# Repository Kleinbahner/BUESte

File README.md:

# BUESte

## Getting parts:
Parts have been put into Reichelt.de parts baskets. Select a basket, specify the number of times you need the parts and put them in your shopping basket.
The following parts lists are available

- [bue: main pcb](https://www.reichelt.de/my/1827413)
- [bue: button boxes](https://www.reichelt.de/my/1832678)
- [bue: detectors](https://www.reichelt.de/my/1832677)
- [bue: cables](https://www.reichelt.de/my/1832680) select the cables suitable for your setup

Lists are also stored [here](https://github.com/Kleinbahner/BUESte/tree/main/doc/reichelt)

## Manuals:
Manual for main pcb assembly: [main pcb manual](https://github.com/Kleinbahner/BUESte/blob/main/doc/Manual%20(DE)%20Bahn%C3%BCbergang%20Platine%20v2.pdf)

Manual for boxes: [boxes manual](https://github.com/Kleinbahner/BUESte/blob/main/doc/Manual-DE-Box.pdf), [drilling template](https://github.com/Kleinbahner/BUESte/blob/main/doc/drill%20template%20bue.pdf)

Manual for detector: to follow

## Software

Manual for programming the Arduino: [Arduino programming](https://github.com/Kleinbahner/BUESte/blob/main/doc/Programmierung%20Arduino%20f%C3%BCr%20Bahn%C3%BCbergangssteuerung.pdf)

## Components
The railway crossing control unit consists of different components that can can be combined in various ways in order to suit the actual module layout requirements. The components will be described in more detail in the following sections.

### Mainboard

The main board is permanently installed near the railroad crossing. All other components are connected to the main board.

The flashing light signals for the railway crossing and the servos for the fences can be connected via terminal blocks. The control inputs are connected to further terminal blocks. There is also an amplifier for connecting a loudspeaker. The sounds can be stored on a microSD card. Power is supplied via an USB socket.

The two RJ45 sockets are used to connect the other components via a looped-through cable. All components can be connected to the same cable in any order. Star cabling is also possible. Alternatively, the inputs and outputs can also be connected directly to the terminal blocks if they are installed in the same module.

#### Pin assignement
All components must be connected to the main board. It has a number of screw and plug connections for this purpose. Ideally, the main board should be mounted near the railroad crossing itself so that many components such as the flashing signals, the light barrier for clear signaling and the loudspeaker can be connected directly. The following illustration provides an overview of the connection options.

The available signals and their meaning are listed here in detail. The output signals for the LED are driven with 5V. Corresponding series resistors must be added yourself!

| Signal | Direction | Activation | Purpose |
| ------ | --------- | ---------- | ------- |
| Loudspeaker | output | - | Connections for a small passive loudspeaker, maximum 1W |
| Servo_1 ... Servo_8 | output | Servo connections for the fences. Pin assignement (from boarder of PCB): - , +, pulse |
| UT-LED_1 | output | LED is on if the current sensor on the left track is disabled by the UT push button |
| UT-LED_2 | output | LED is on if the current sensor on the right track is disabled by the UT push button |
| Uebsig_1 | output | LED for the flashing signals of the left track |
| Uebsig_2 | output | LED for the flashing signals of the right track |
| Blink_1 ... Blink_4 | output | Flashing signals for the railroad crossing.  Blink_1 and 2 are phase shifted to Blink_3 and 4 |
| Bus_1 | output | Signals to attached remote components on the left track |
| Bus_2 | output | Signals to attached remote components on the right track |
| Strom_1 | input | LOW active | Input for the current sensor of the left track |
| Strom_2 | input | LOW active | Input for the current sensor of the right track |
| Lichtschranke | input | HIGH active | Input for the light barrier for clear signaling of the railroad crossing |
| UT_1 | input | LOW active | Input to temporary deactivate the current sensor on the left track |
| UT_2 | input | LOW active | Input to temporary deactivate the current sensor on the right track |
| RS | input | LOW active | Input for the "Rangierschalter" (RS) |
| AT | input | LOW active | Input for the disable push button (AT) |
| ET | input | LOW active | Input for the enable push button (ET) |
| USB Power | input | - | Power supply for the circuit. A power bank is recommended to be independent of outlets. |
| 5V | output | - | Supply voltage for light barrier |
| Masse | - | - | Common potential for push buttons |
| Config (only v1_0) | - | - | Actually not used. Can be used for further extensions. |
| I2C (only v2_0) | - | - |  I2C bus of the arudino. For further extensions. |
| Erweiterung 1 (only v2_0) | - | - | Unused pins of the arduino. Actualy not used. |
| Erweiterung 2 (only v2_0) | - | - | Unused pins of the arduino. Actualy not used. |
| SD-Karte | - | - | Slot for SD card. The card has to contain the WAV file for the signal sound. Attention: There has to be a card in the slot with a WAV file called "ding.wav" in the main directory. Otherwise the control unit will not work! |

#### Assignement of the bus cable
A bus is used to connect the components further away from the main board. All the required signals are routed in a single multi-core cable. An RJ45 cable is used for this. Starting from the main board, all components are connected to each other. The boxes have three sockets and can therefore be used as splitters. All sockets are of equal value. The cabling can be carried out in any combination. Only the left and right sections need to be differentiated as the disable buttons, the sensors and the supervision signals are direction dependent. Examples of wiring can be found below under examples.

The socket is assigned as follows (view into the socket):

| Pin | Function |
| --- | -------- |
| 1 | Ground |
| 2 | Enable push button (ET) |
| 3 | Disable push button (AT) |
| 4 | Shunting switch (RS) |
| 5 | Disable current sensor push button (UT) |
| 6 | LED to mark disabled current sensor |
| 7 | LED for supervision signal. Blinks in phase with flashing light signal |
| 8 | Current sensor |

### Enable box
For manual operation of the railraod crossing a small box is needed. It contains the Enable (ET) and Disable (AT) push buttons as well as a shunting switch. The shunting switch can be equiped with an LED that blinks in phase with the flashing light signal to mark its use.

The box can be attached to modules using the well know FREMO-Clamps. The box contains a hole for that purpose.

The connection from the box to the mainboard is through a RJ-45 cable (straight) as it is known from computer networks. Each box has three equal sockets. Thus it can also be used as splitter for cabling.

To ease the cabling inside the box, a small PCB has been designed. It fits perfectly in the boxes used and provides space for three RJ-45 sockets. In addition it provides soldering points for the push buttons and the LEDs.

### Current sensor
The current sensor is based on the design of Reinhard Müller [http://dcc-mueller.de/wire4dcc/sensor_d.htm](http://dcc-mueller.de/wire4dcc/sensor_d.htm), that has been expanded with a RJ-45 socket for the crossing cabling system.

The purpose of the current sensor is the detection of an approaching train. In order to do that one rail of a module is isolated from the neigboring modules (module interconnection cable not pluged in). This rail is then supplied through the current sensor that is attached to the neigboring module. There are no changes of the modules required.

### Sensor box
Near to the current sensor, a sensor box can be attached to the modules using FREMO-clamps. The box can also serve als signal splitter.

The main purpose of this box is to provide the disable button near to the current sensor. By pressing the push button, the current sensor will be disabled for a give time period. A disabled current sensor is signaled by the LED in the box. Deactivation of the sensor can be necessary if there are shunting activities ongoing that would touch the module with the sensor without the need to close the railway crossing.

### Supervision signal
The engine driver needs to know if the railraod crossing is correctly enabled. That is the purpose of the supervision signal that is placed after the current sensor that turns the railroad crossing on. If the railroad crossing is enabled the signal will be blinking.

The supervision signal is placed in a Wattenscheider signal carrier and thus can be placed in any module with the propper Wattenscheiderslot. The signal is connected to the main board using an RJ45-socket. If an additional marker light should be realised, there has to be a sperate power supply. This can for example be done by including a battery and a voltage regulator in the signal carrier.

## Module setup
The components presented before allow for a flexible setup. Two example setups will be presented here.

### Railraod crossing on open track
The most simple case is a railway crossing on clear track. There the main board is integrated in the module which contains the railway crossing and crossing lights. The flashing signal lights, maybe existing fences and the speaker are then directly connected to the main board. Left and right of the railraod crossing on the module at a sufficient distance a sensor module is used. One rail will be isolated from the other modules and will be supplied through a current sensor. The sensor is connected to the main board using RJ45-cables.

To connect the supervising signals it is recommended to install a sensor box near to every current sensor. The boxes are then used as splitters to connect both the current sensor and the signal.
In this setup the railroad crossing is controlled only by the trains, no interaction of the driver is required.

### Railroad crossing at the end of a station
The situation gets more complex if the railroway crossing is located at the end of a station where trains stop. In this case the railroad crossing can not only be automatically engaged by a current sensor at the side of the station. This could be the case if a train approaches to station to make sure that the crossing is stil secured if the train does not correctly stop at the platform.

As soon as the trains stops, the railway crossing will be deactivated manually using the Einschaltbox to allow road users to use the crossing when the train is stooped at station. Before the trains continue their journey, the crossing has to be enabled again manually. Therefore an Einschaltbox is required.
In addition the box contains the shunting switch. This is switched on if there are shunting activities ongoing that will involve the railway crossing. The lights are then permanently switched on and will only turn off after the shunting switch has been switched off.

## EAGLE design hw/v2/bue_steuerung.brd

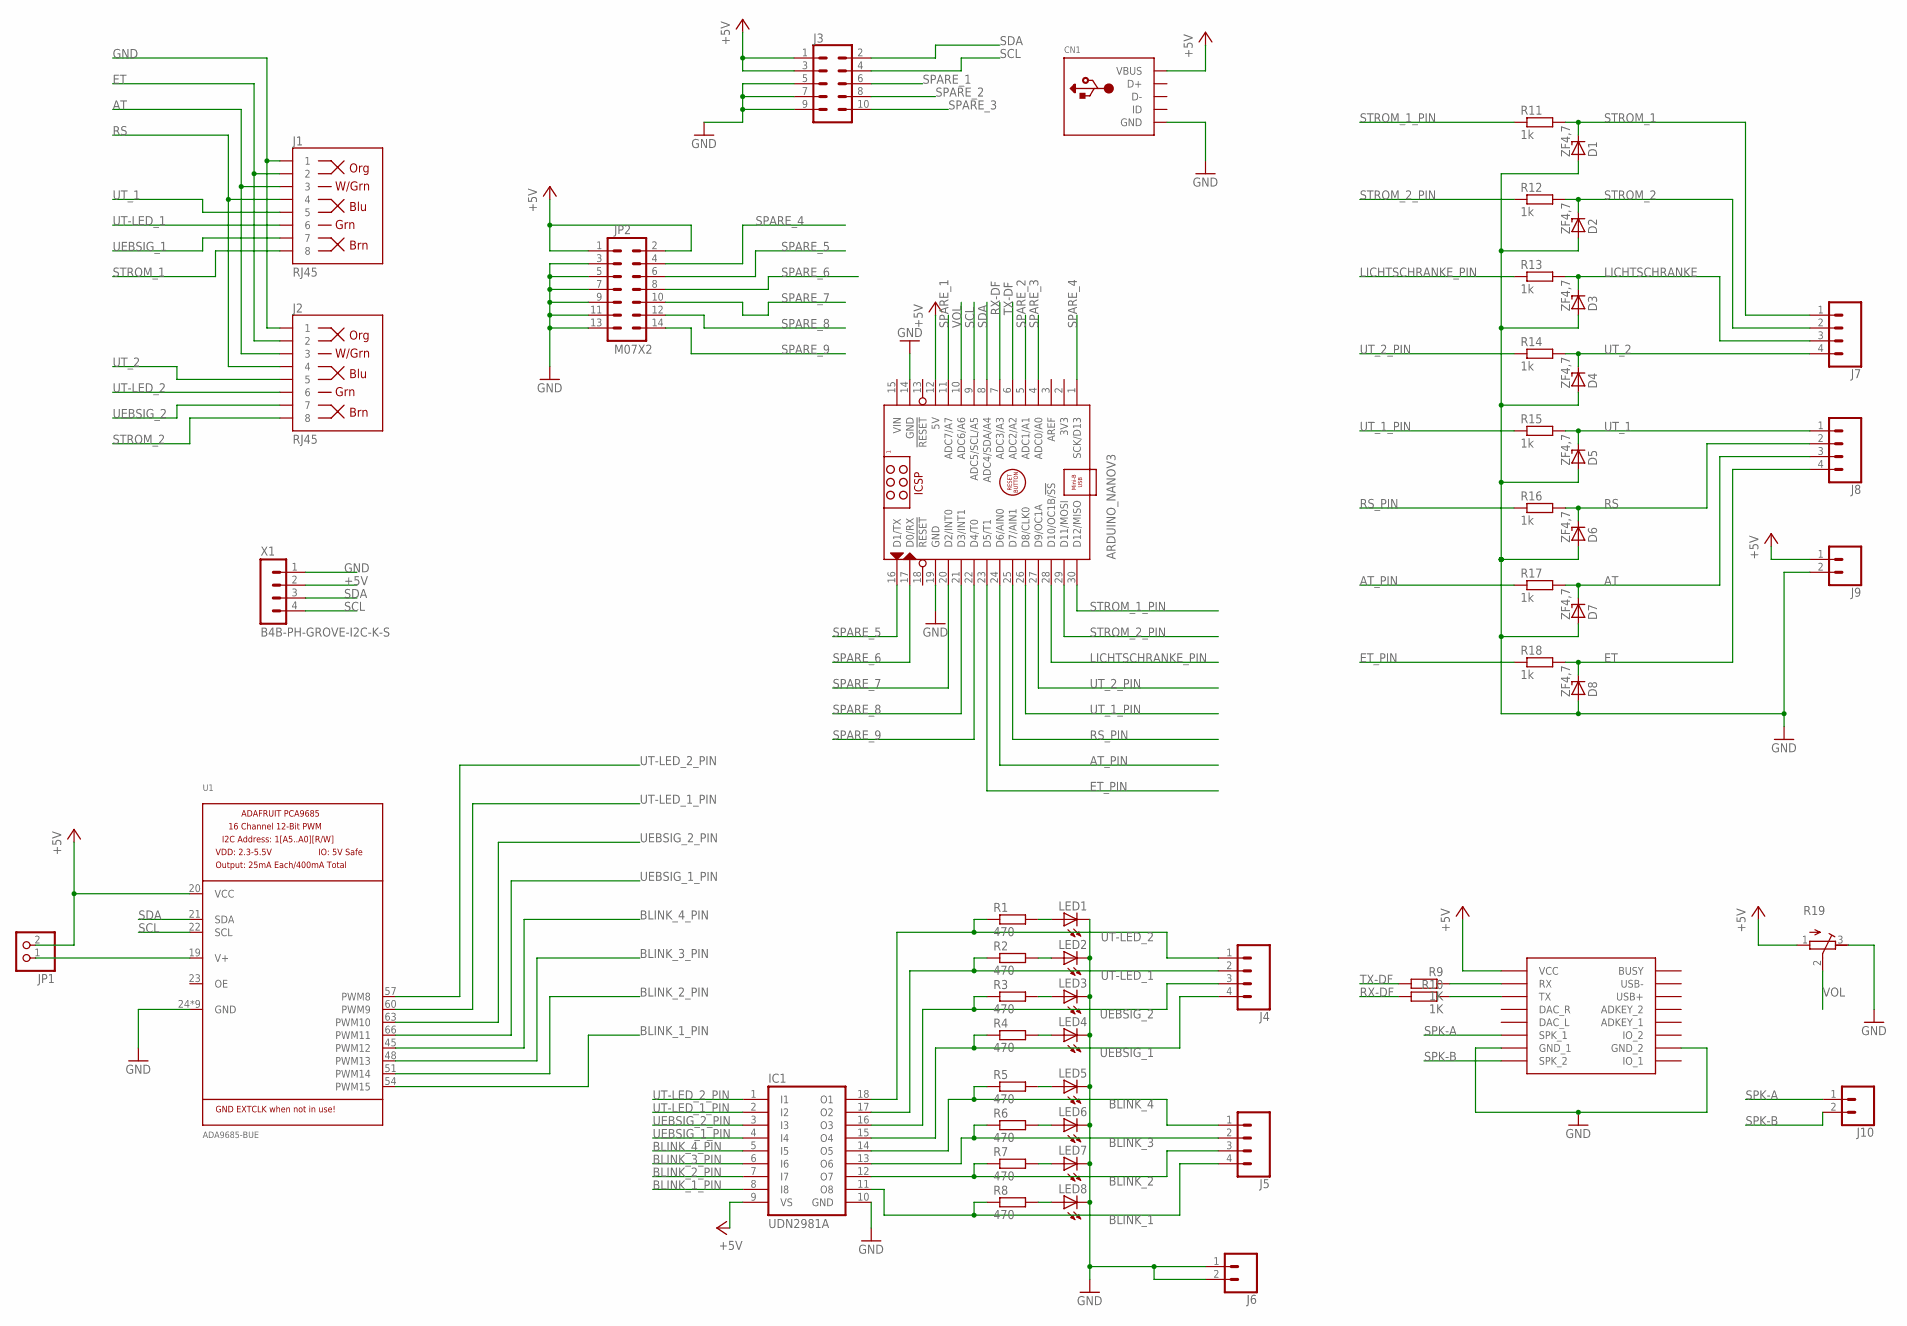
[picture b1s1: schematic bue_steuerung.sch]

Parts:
ARDUINO_NANOV3: ARDUINO_NANO
CN1: USBMOLEX; USB-MINIB-THM-MOLEX
D1, D2, D3, D4, D5, D6, D7, D8: ZF4,7; ZDIO-7.5
IC1: UDN2981A; DIL18
J1, J2: RJ45; RJ45-8
J3: CONN_05X2SHD; 2X5-SHROUDED
J4, J5, J7, J8: CONN_04SCREW; SCREWTERMINAL-3.5MM-4
J6, J9, J10: CONN_023.5MM; SCREWTERMINAL-3.5MM-2
JP1: PINHD-1X2; 1X02
JP2: M07X2; 2X7-SHROUDED
LED1, LED2, LED3, LED4, LED5, LED6, LED7, LED8: LED3MM
R1, R2, R3, R4, R5, R6, R7, R8: 470; 0207/7
R9, R10: 1K; 0207/7
R11, R12, R13, R14, R15, R16, R17, R18: 1k; 0207/7
R19: R-TRIMM64Y; RTRIM64Y
U1: ADA9685-BUE
U2: DFPLAYER
X1: B4B-PH-GROVE-I2C-K-S; B4B-PH-K-S

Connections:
+5V: ARDUINO_NANOV3.12 (5V), CN1.VBUS, IC1.9 (VS), J3.1, J3.3, J9.1, JP1.2, JP2.1, JP2.2, R19.1 (A), U1.20 (VCC), U2.VCC, X1.2 (3)
AT: D7.C, J1.3, J2.3, J8.3, R17.2
AT_PIN: ARDUINO_NANOV3.24 (D6/AIN0), R17.1
BLINK_1: IC1.11 (O8), J5.4, R8.1
BLINK_1_PIN: IC1.8 (I8), U1.54 (PWM15)
BLINK_2: IC1.12 (O7), J5.3, R7.1
BLINK_2_PIN: IC1.7 (I7), U1.51 (PWM14)
BLINK_3: IC1.13 (O6), J5.2, R6.1
BLINK_3_PIN: IC1.6 (I6), U1.48 (PWM13)
BLINK_4: IC1.14 (O5), J5.1, R5.1
BLINK_4_PIN: IC1.5 (I5), U1.45 (PWM12)
ET: D8.C, J1.2, J2.2, J8.4, R18.2
ET_PIN: ARDUINO_NANOV3.23 (D5/T1), R18.1
GND: ARDUINO_NANOV3.14 (GND), ARDUINO_NANOV3.19 (GND), CN1.GND, D1.A, D2.A, D3.A, D4.A, D5.A, D6.A, D7.A, D8.A, IC1.10 (GND), J1.1, J2.1, J3.5, J3.7, J3.9, J6.1, J6.2, J9.2, JP2.3, JP2.5, JP2.7, JP2.9, JP2.11, JP2.13, LED1.K (C), LED2.K (C), LED3.K (C), LED4.K (C), LED5.K (C), LED6.K (C), LED7.K (C), LED8.K (C), R19.3 (E), U1.24 (GND), U1.43 (GND), U1.46 (GND), U1.49 (GND), U1.52 (GND), U1.55 (GND), U1.58 (GND), U1.61 (GND), U1.64 (GND), U2.GND_1, U2.GND_2, X1.1 (4)
LICHTSCHRANKE: D3.C, J7.3, R13.2
LICHTSCHRANKE_PIN: ARDUINO_NANOV3.28 (D10/OC1B/!SS), R13.1
unnamed: JP1.1, U1.19 (V+)
unnamed: LED4.A, R4.2
unnamed: R9.1, U2.RX
unnamed: R10.1, U2.TX
unnamed: LED8.A, R8.2
unnamed: LED7.A, R7.2
unnamed: LED6.A, R6.2
unnamed: LED5.A, R5.2
unnamed: LED3.A, R3.2
unnamed: LED2.A, R2.2
unnamed: LED1.A, R1.2
RS: D6.C, J1.4, J2.4, J8.2, R16.2
RS_PIN: ARDUINO_NANOV3.25 (D7/AIN1), R16.1
RX-DF: ARDUINO_NANOV3.7 (ADC3/A3), R10.2
SCL: ARDUINO_NANOV3.9 (ADC5/SCL/A5), J3.4, U1.22 (SCL), X1.4 (1)
SDA: ARDUINO_NANOV3.8 (ADC4/SDA/A4), J3.2, U1.21 (SDA), X1.3 (2)
SPARE_1: ARDUINO_NANOV3.11 (ADC7/A7), J3.6
SPARE_2: ARDUINO_NANOV3.5 (ADC1/A1), J3.8
SPARE_3: ARDUINO_NANOV3.4 (ADC0/A0), J3.10
SPARE_4: ARDUINO_NANOV3.1 (SCK/D13), JP2.4
SPARE_5: ARDUINO_NANOV3.16 (D1/TX), JP2.6
SPARE_6: ARDUINO_NANOV3.17 (D0/RX), JP2.8
SPARE_7: ARDUINO_NANOV3.20 (D2/INT0), JP2.10
SPARE_8: ARDUINO_NANOV3.21 (D3/INT1), JP2.12
SPARE_9: ARDUINO_NANOV3.22 (D4/T0), JP2.14
SPK-A: J10.1, U2.SPK1 (SPK_1)
SPK-B: J10.2, U2.SPK2 (SPK_2)
STROM_1: D1.C, J1.8, J7.1, R11.2
STROM_1_PIN: ARDUINO_NANOV3.30 (D12/MISO), R11.1
STROM_2: D2.C, J2.8, J7.2, R12.2
STROM_2_PIN: ARDUINO_NANOV3.29 (D11/MOSI), R12.1
TX-DF: ARDUINO_NANOV3.6 (ADC2/A2), R9.2
UEBSIG_1: IC1.15 (O4), J1.7, J4.4, R4.1
UEBSIG_1_PIN: IC1.4 (I4), U1.66 (PWM11)
UEBSIG_2: IC1.16 (O3), J2.7, J4.3, R3.1
UEBSIG_2_PIN: IC1.3 (I3), U1.63 (PWM10)
UT-LED_1: IC1.17 (O2), J1.6, J4.2, R2.1
UT-LED_1_PIN: IC1.2 (I2), U1.60 (PWM9)
UT-LED_2: IC1.18 (O1), J2.6, J4.1, R1.1
UT-LED_2_PIN: IC1.1 (I1), U1.57 (PWM8)
UT_1: D5.C, J1.5, J8.1, R15.2
UT_1_PIN: ARDUINO_NANOV3.26 (D8/CLK0), R15.1
UT_2: D4.C, J2.5, J7.4, R14.2
UT_2_PIN: ARDUINO_NANOV3.27 (D9/OC1A), R14.1
VIN: ARDUINO_NANOV3.15 (VIN)
VOL: ARDUINO_NANOV3.10 (ADC6/A6), R19.2 (S)

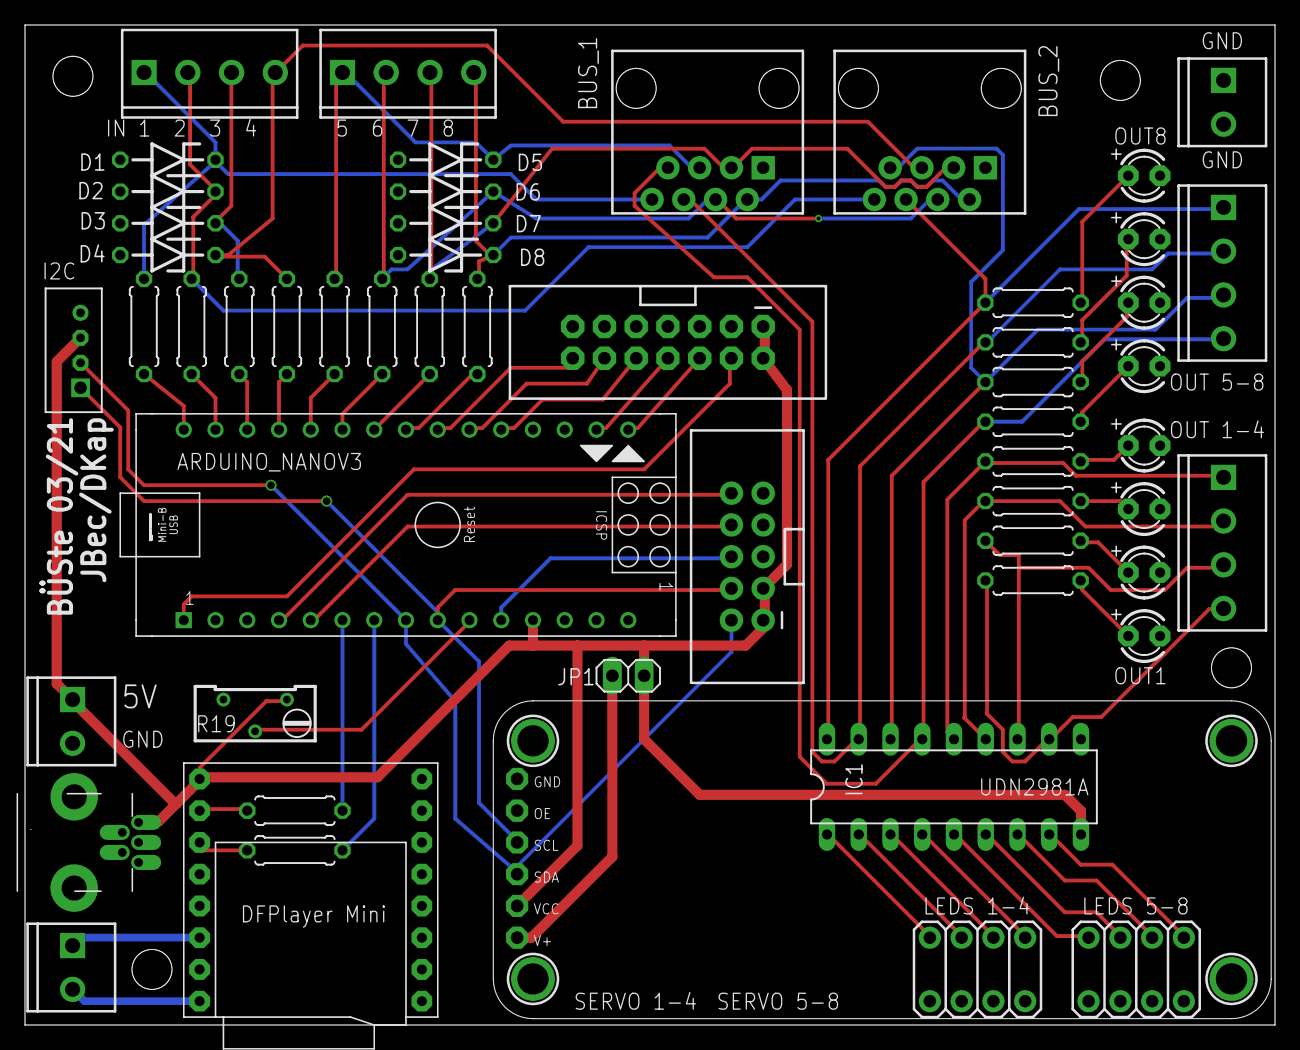
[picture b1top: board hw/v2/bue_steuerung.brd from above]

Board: 2 copper layers, 100.0 x 80.0 mm, 53 parts (0 on the bottom side), 61 nets.

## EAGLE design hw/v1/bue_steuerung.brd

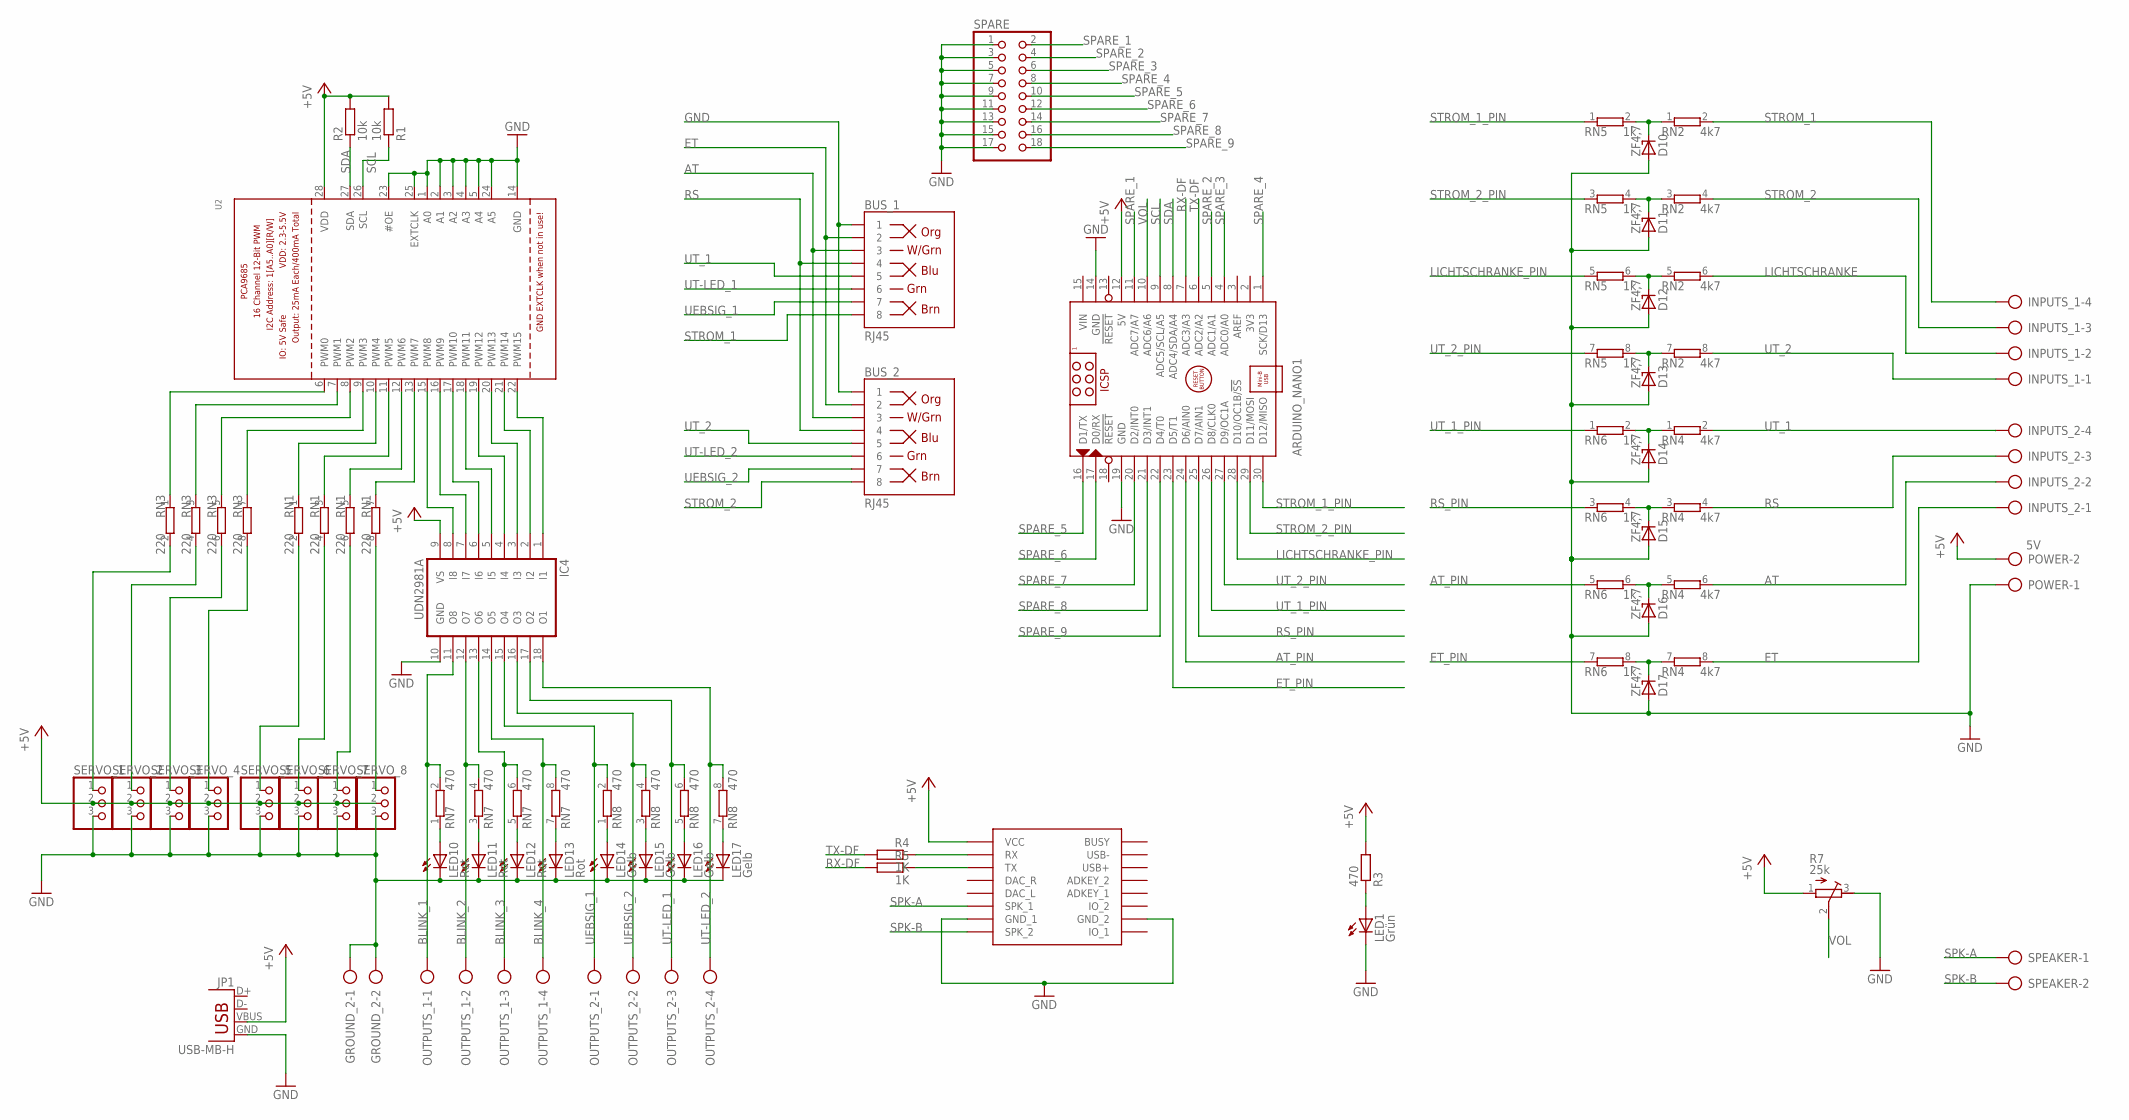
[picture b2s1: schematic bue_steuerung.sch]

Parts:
ARDUINO_NANO1: ARDUINO_NANO
BUS_1, BUS_2: RJ45; RJ45-8
D10, D17: ZF4,7; ZDIO-2.5
D11, D16: ZF4,7; ZDIO-5
D12, D15: ZF4,7; ZDIO-10
D13, D14: ZF4,7; ZDIO12.5
GROUND_2: AK500/2
IC4: UDN2981A; DIL18
INPUTS_1, INPUTS_2: AK500/4
JP1: USB-MB-H
LED1: Grün; LED3MM
LED10, LED11, LED12, LED13: Rot; LED3MM
LED14, LED15, LED16, LED17: Gelb; LED3MM
OUTPUTS_1, OUTPUTS_2: AK500/4
POWER: 5V; AK500/2
R1, R2: 10k; 0207/10
R3: 470; 0207/10
R4, R5: 1K; 0207/10
R7: 25k; RTRIM64Z
RN1, RN3: 220; SIL8
RN2, RN4: 4k7; SIL8
RN5, RN6: 1k; SIL8
RN7, RN8: 470; SIL8
SERVO_1, SERVO_2, SERVO_3, SERVO_4, SERVO_5, SERVO_6, SERVO_7, SERVO_8: PINHD-1X3; 1X03
SPARE: PINHD-2X9; 2X09
SPEAKER: AK500/2
U2: PCA9685; TSSOP28
U$1: DFPLAYER

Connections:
+5V: ARDUINO_NANO1.12 (5V), IC4.9 (VS), JP1.VBUS, POWER.2, R1.2, R2.2, R3.2, R7.1 (E), SERVO_1.2, SERVO_2.2, SERVO_3.2, SERVO_4.2, SERVO_5.2, SERVO_6.2, SERVO_7.2, SERVO_8.2, U2.28 (VDD), U$1.VCC
AT: BUS_1.3, BUS_2.3, INPUTS_2.2, RN4.6 (2)
AT_PIN: ARDUINO_NANO1.24 (D6/AIN0), RN6.5 (1)
BLINK_1: IC4.11 (O8), OUTPUTS_1.1, RN7.2
BLINK_2: IC4.12 (O7), OUTPUTS_1.2, RN7.4 (2)
BLINK_3: IC4.13 (O6), OUTPUTS_1.3, RN7.6 (2)
BLINK_4: IC4.14 (O5), OUTPUTS_1.4, RN7.8 (2)
ET: BUS_1.2, BUS_2.2, INPUTS_2.1, RN4.8 (2)
ET_PIN: ARDUINO_NANO1.23 (D5/T1), RN6.7 (1)
GND: ARDUINO_NANO1.14 (GND), ARDUINO_NANO1.19 (GND), BUS_1.1, BUS_2.1, D10.A, D11.A, D12.A, D13.A, D14.A, D15.A, D16.A, D17.A, GROUND_2.1, GROUND_2.2, IC4.10 (GND), JP1.GND, LED1.K (C), LED10.K (C), LED11.K (C), LED12.K (C), LED13.K (C), LED14.K (C), LED15.K (C), LED16.K (C), LED17.K (C), POWER.1, R7.3 (A), SERVO_1.3, SERVO_2.3, SERVO_3.3, SERVO_4.3, SERVO_5.3, SERVO_6.3, SERVO_7.3, SERVO_8.3, SPARE.1, SPARE.3, SPARE.5, SPARE.7, SPARE.9, SPARE.11, SPARE.13, SPARE.15, SPARE.17, U2.1 (A0), U2.2 (A1), U2.3 (A2), U2.4 (A3), U2.5 (A4), U2.14 (GND), U2.23 (#OE), U2.24 (A5), U2.25 (EXTCLK), U$1.GND_1, U$1.GND_2
LICHTSCHRANKE: INPUTS_1.2, RN2.6 (2)
LICHTSCHRANKE_PIN: ARDUINO_NANO1.28 (D10/OC1B/!SS), RN5.5 (1)
unnamed: RN1.4 (2), SERVO_6.1
unnamed: RN1.6 (2), SERVO_7.1
unnamed: RN1.8 (2), SERVO_8.1
unnamed: IC4.8 (I8), U2.15 (PWM8)
unnamed: LED14.A, RN8.1
unnamed: LED1.A, R3.1
unnamed: R4.1, U$1.RX
unnamed: IC4.7 (I7), U2.16 (PWM9)
unnamed: R5.1, U$1.TX
unnamed: D17.C, RN4.7 (1), RN6.8 (2)
unnamed: D14.C, RN4.1, RN6.2
unnamed: D16.C, RN4.5 (1), RN6.6 (2)
unnamed: D15.C, RN4.3 (1), RN6.4 (2)
unnamed: D12.C, RN2.5 (1), RN5.6 (2)
unnamed: D11.C, RN2.3 (1), RN5.4 (2)
unnamed: D10.C, RN2.1, RN5.2
unnamed: D13.C, RN2.7 (1), RN5.8 (2)
unnamed: IC4.6 (I6), U2.17 (PWM10)
unnamed: IC4.5 (I5), U2.18 (PWM11)
unnamed: IC4.4 (I4), U2.19 (PWM12)
unnamed: IC4.3 (I3), U2.20 (PWM13)
unnamed: RN3.2, SERVO_1.1
unnamed: RN3.4 (2), SERVO_2.1
unnamed: RN3.6 (2), SERVO_3.1
unnamed: RN3.8 (2), SERVO_4.1
unnamed: RN1.2, SERVO_5.1
unnamed: IC4.2 (I2), U2.21 (PWM14)
unnamed: IC4.1 (I1), U2.22 (PWM15)
unnamed: LED10.A, RN7.1
unnamed: LED11.A, RN7.3 (1)
unnamed: LED12.A, RN7.5 (1)
unnamed: RN3.1, U2.6 (PWM0)
unnamed: RN3.3 (1), U2.7 (PWM1)
unnamed: RN3.5 (1), U2.8 (PWM2)
unnamed: RN3.7 (1), U2.9 (PWM3)
unnamed: RN1.1, U2.10 (PWM4)
unnamed: RN1.3 (1), U2.11 (PWM5)
unnamed: RN1.5 (1), U2.12 (PWM6)
unnamed: RN1.7 (1), U2.13 (PWM7)
unnamed: LED13.A, RN7.7 (1)
unnamed: LED15.A, RN8.3 (1)
unnamed: LED16.A, RN8.5 (1)
unnamed: LED17.A, RN8.7 (1)
RS: BUS_1.4, BUS_2.4, INPUTS_2.3, RN4.4 (2)
RS_PIN: ARDUINO_NANO1.25 (D7/AIN1), RN6.3 (1)
RX-DF: ARDUINO_NANO1.7 (ADC3/A3), R5.2
SCL: ARDUINO_NANO1.9 (ADC5/SCL/A5), R1.1, U2.26 (SCL)
SDA: ARDUINO_NANO1.8 (ADC4/SDA/A4), R2.1, U2.27 (SDA)
SPARE_1: ARDUINO_NANO1.11 (ADC7/A7), SPARE.2
SPARE_2: ARDUINO_NANO1.5 (ADC1/A1), SPARE.4
SPARE_3: ARDUINO_NANO1.4 (ADC0/A0), SPARE.6
SPARE_4: ARDUINO_NANO1.1 (SCK/D13), SPARE.8
SPARE_5: ARDUINO_NANO1.16 (D1/TX), SPARE.10
SPARE_6: ARDUINO_NANO1.17 (D0/RX), SPARE.12
SPARE_7: ARDUINO_NANO1.20 (D2/INT0), SPARE.14
SPARE_8: ARDUINO_NANO1.21 (D3/INT1), SPARE.16
SPARE_9: ARDUINO_NANO1.22 (D4/T0), SPARE.18
SPK-A: SPEAKER.1, U$1.SPK1 (SPK_1)
SPK-B: SPEAKER.2, U$1.SPK2 (SPK_2)
STROM_1: BUS_1.8, INPUTS_1.4, RN2.2
STROM_1_PIN: ARDUINO_NANO1.30 (D12/MISO), RN5.1
STROM_2: BUS_2.8, INPUTS_1.3, RN2.4 (2)
STROM_2_PIN: ARDUINO_NANO1.29 (D11/MOSI), RN5.3 (1)
TX-DF: ARDUINO_NANO1.6 (ADC2/A2), R4.2
UEBSIG_1: BUS_1.7, IC4.15 (O4), OUTPUTS_2.1, RN8.2
UEBSIG_2: BUS_2.7, IC4.16 (O3), OUTPUTS_2.2, RN8.4 (2)
UT-LED_1: BUS_1.6, IC4.17 (O2), OUTPUTS_2.3, RN8.6 (2)
UT-LED_2: BUS_2.6, IC4.18 (O1), OUTPUTS_2.4, RN8.8 (2)
UT_1: BUS_1.5, INPUTS_2.4, RN4.2
UT_1_PIN: ARDUINO_NANO1.26 (D8/CLK0), RN6.1
UT_2: BUS_2.5, INPUTS_1.1, RN2.8 (2)
UT_2_PIN: ARDUINO_NANO1.27 (D9/OC1A), RN5.7 (1)
VIN: ARDUINO_NANO1.15 (VIN)
VOL: ARDUINO_NANO1.10 (ADC6/A6), R7.2 (S)

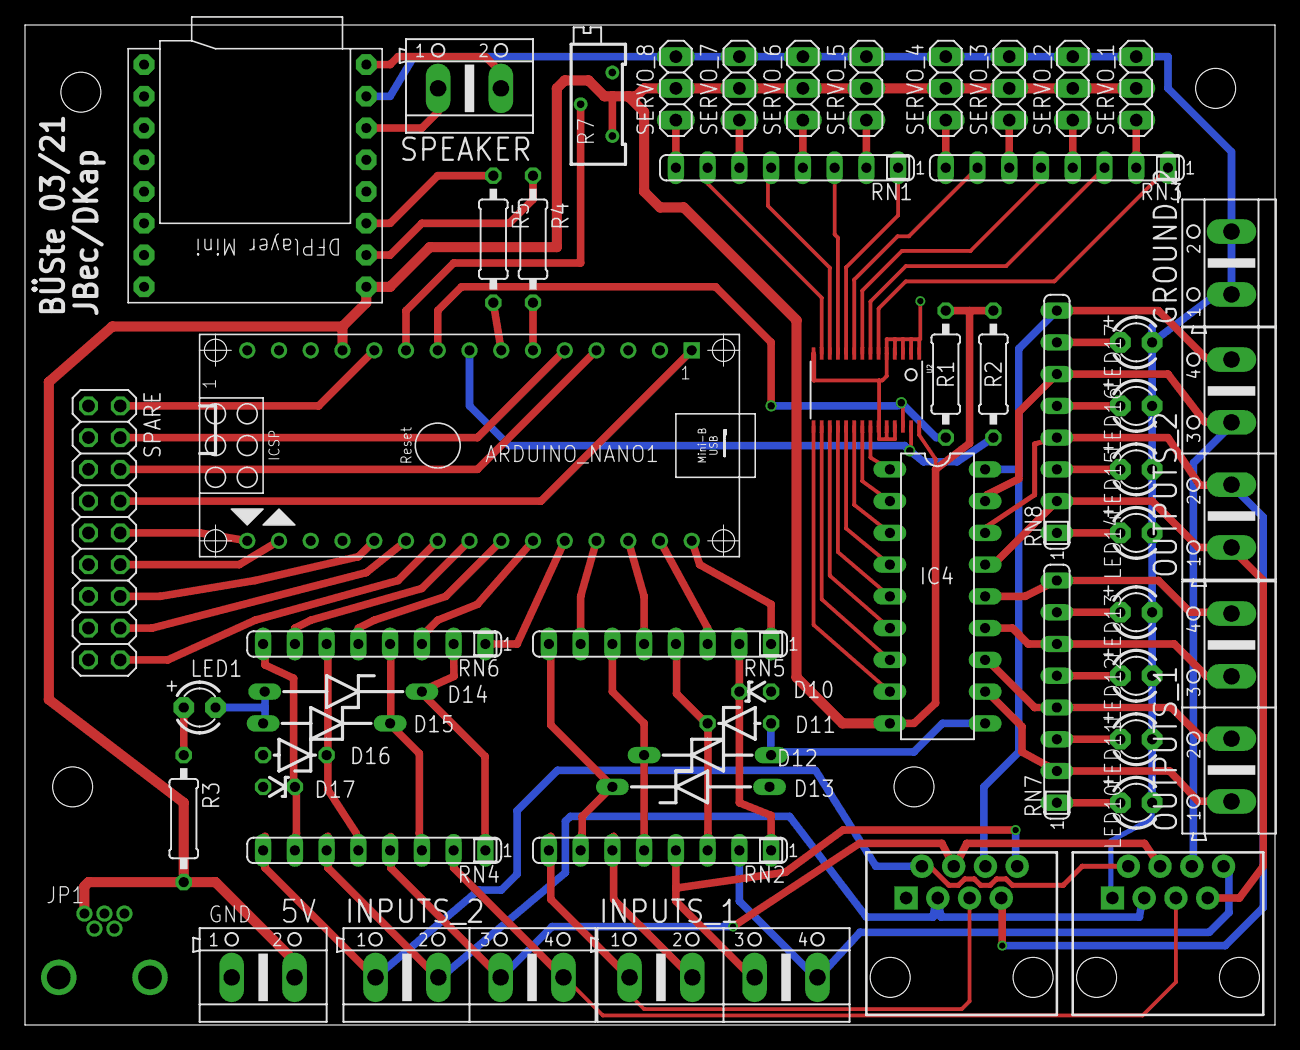
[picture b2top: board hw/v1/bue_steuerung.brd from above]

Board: 2 copper layers, 100.0 x 80.0 mm, 54 parts (0 on the bottom side), 85 nets.

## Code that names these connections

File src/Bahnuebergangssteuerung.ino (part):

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#define DFPlayer_TX A2

// Eingangspins
#define ET_PIN 5                    // Einschalttaster
#define UT1_PIN 8                   // Unwirksamkeitstaster rechts
#define UT2_PIN 9                   // Unwirksamkeitstaster links
#define AT_PIN 6                    // Ausschalttaster
#define RS_PIN 7                    // Rangierschalter
#define Strom1_PIN 12               // Stromsensor rechts
#define Strom2_PIN 11               // Stromsensor links
#define LS_PIN 10                   // Freimeldung des Bahnübergangs (Lichtschranke)

#define volume_PIN A6                // Anschluss fuer den Poti zur Lautstärkeregelung

// Eingänge konfigurieren
Button ET = Button(ET_PIN, LOW);            // Einschalttaster
Button UT1 = Button(UT1_PIN, LOW);          // Unwirksamkeitstaster rechts
Button UT2 = Button(UT2_PIN, LOW);          // Unwirksamkeitstaster links
Button AT = Button(AT_PIN, LOW);            // Ausschalttaster
Button RS = Button(RS_PIN, LOW);            // Rangierschalter
Button Strom1 = Button(Strom1_PIN, LOW);    // Stromsensor rechts
Button Strom2 = Button(Strom2_PIN, LOW);    //Stromsensor links
//Button LS = Button(LS_PIN, HIGH);           // Freimeldung des Bahnübergangs
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void setup() {
  // put your setup code here, to run once:
  
  pinMode(ET_PIN, INPUT_PULLUP);
  pinMode(UT1_PIN, INPUT_PULLUP);
  pinMode(UT2_PIN, INPUT_PULLUP);
  pinMode(AT_PIN, INPUT_PULLUP);
  pinMode(RS_PIN, INPUT_PULLUP);
  pinMode(Strom1_PIN, INPUT_PULLUP);
  pinMode(Strom2_PIN, INPUT_PULLUP);
  pinMode(LS_PIN, INPUT_PULLUP);
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
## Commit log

2021-05-17 added manuals
    add drill template and pcb soldering manual
2021-05-17 added ordering lists
    added Reichel csv files for direct ordering components
2021-05-22 Create LICENSE
2021-10-08 Create Bahnuebergangssteuerung.ino
    Software version published
2021-10-11 Programming instructions for Arduino
2021-10-11 added Arduino programming
2021-10-16 dffast driver
2021-10-18 Revert "Delete Programmierung Arduino für Bahnübergangssteuerung.pdf"
    This reverts commit 76058ff07bfd1d54a2f4ac115b1b7e38dc75fe13.
2021-12-06 hw3
    Loconet and bord redesign
2022-08-26 Added HW and SW versions 1 and 2
2023-01-09 Create bue-platine-io.docx
    io ports explanation
2024-12-27 Description of components and setups, include pictures
2024-12-31 Update README.md
    revised language and spelling errors
2026-05-25 translation
    all comment

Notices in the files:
parts and their libraries:
SparkFun-Connectors: Licensing: Creative Commons ShareAlike 4.0 International - https://creativecommons.org/licenses/by-sa/4.0
